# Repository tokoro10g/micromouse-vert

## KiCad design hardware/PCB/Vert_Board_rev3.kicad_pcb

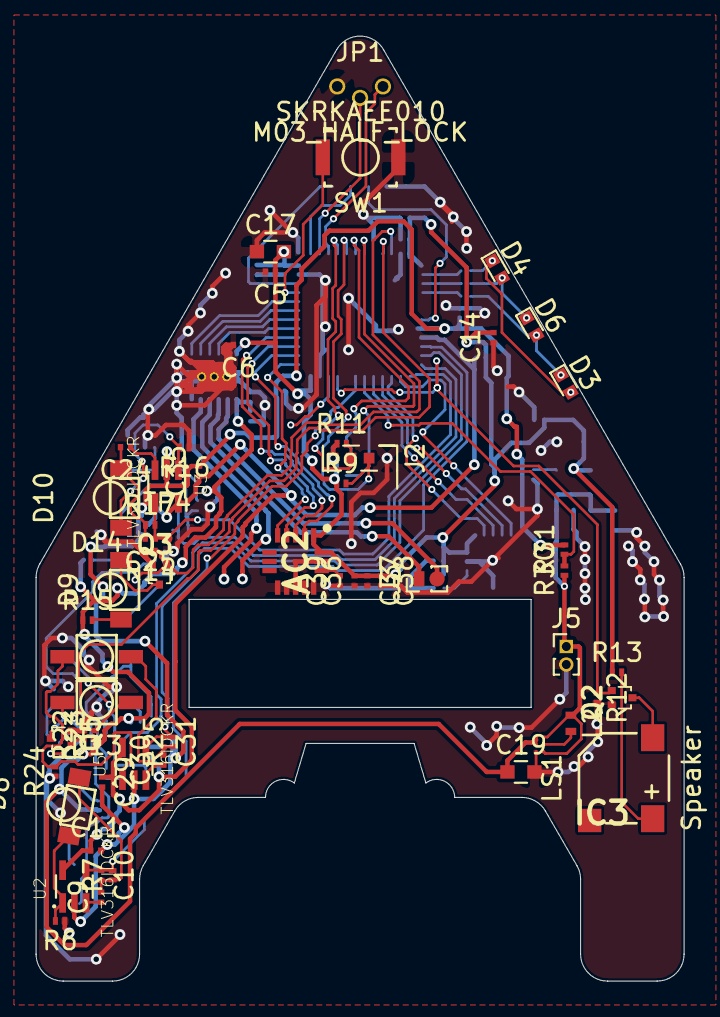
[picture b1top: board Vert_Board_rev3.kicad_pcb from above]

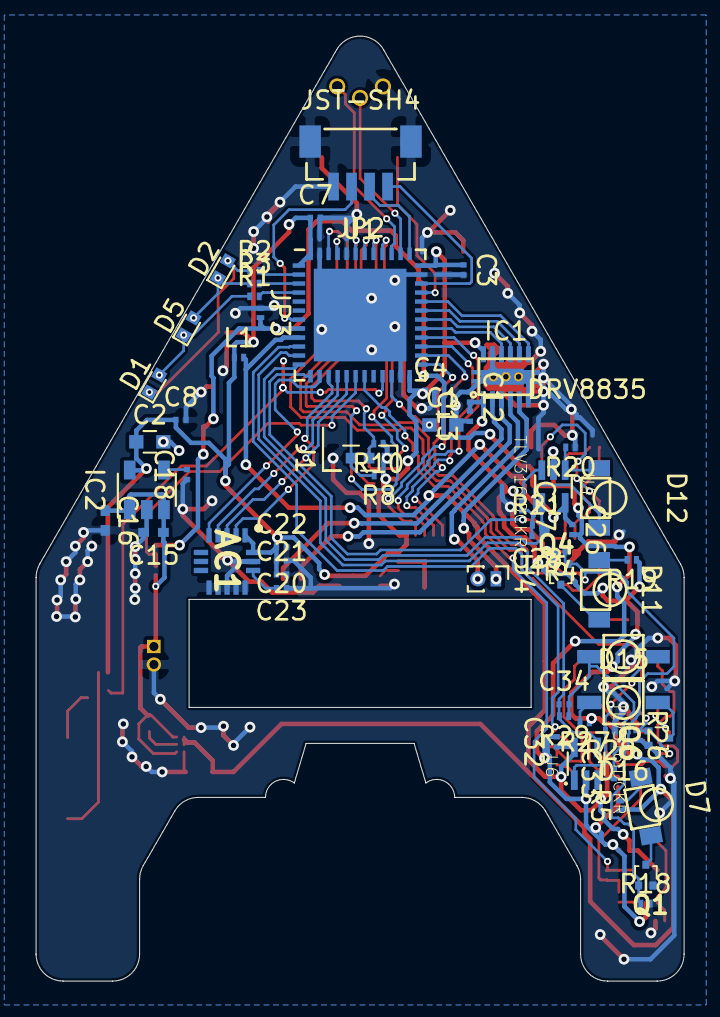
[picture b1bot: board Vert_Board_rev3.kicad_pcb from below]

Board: 4 copper layers, 36.0 x 52.5 mm, 117 parts (59 on the bottom side), 79 nets.

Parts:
AC1, AC2: ICM-20602; QFN50P300X300X75-16N
C1, C2, C19: 4.7u; C_0603
C3, C4, C5, C6, C7, C8, C11, C12, C14, C21, C23, C26, C29, C32, C35, C37, C39: 0.1u; C_0201_NoSilk
C9, C24, C27, C30, C33: 0.01u(NC); C_0201_NoSilk
C10, C25, C28, C31, C34: 22p; C_0201_NoSilk
C13: 22u; C_0201_NoSilk
C15: 2.2u; C_0402_NoSilk
C16: 1u; C_0402_NoSilk
C17: 10u; C_0603
C18, C20, C36: 0.01u; C_0201_NoSilk
C22, C38: 2.2u; C_0201_NoSilk
D1, D2, D3, D4, D5, D6: LED; LED_0402
D7, D9, D11: VSMB294008G; VSMB2943SL
D8, D10, D12: VEMD2020X01; VEMD2023SL
D13, D15: VSMB294008G
D14, D16: VEMD2020X01; VEMD2020
IC1: DRV8835
IC2: TAR5SB33; SOT-23-5
IC3: TPS6124x; BGA6C40P2X3_125X85X63
J1, J2: Conn_01x04; Pin_Header_Straight_1x04_Pitch1.00mm_SMD_Pin1Right
J3, J4, J5: Conn_01x02; Pin_Header_Straight_1x02_Pitch1.00mm
JP1: M03_HALF_LOCK
JP2: JST-SH4
JP3: Jumper_NC_Small; R_0201_NoSilk
L1: 10Z; R_0201_NoSilk
L2: 1u; R_0402_NoSilk
LS1: Speaker; SMT-0540-S-R
Q1, Q3, Q4, Q5, Q6: NTK3134NT1G; SOT-723
Q2: Q_NMOS_GSD; SOT-723
R1, R2, R3: 470; R_0201_NoSilk
R4, R8, R9, R10, R11, R12, R14, R18, R22, R26: 47k; R_0201_NoSilk
R5, R15, R19, R23, R27: 20; R_0201_NoSilk
R6, R16, R20, R24, R28, R30, R31: 500k; R_0201_NoSilk
R7, R17, R21, R25, R29: 1M; R_0201_NoSilk
R13: 22; R_0201_NoSilk
SW1: SKRKAEE010; ALPS-SKRK
TP4, TP6: TEST; Measurement_Point_Round-SMD-Pad_Small
U1: STM32F411CEUx; QFN-48-1EP_7x7mm_Pitch0.5mm
U2, U3, U4, U5, U6: TLV316IDCKR; SOT65P210X110-5N

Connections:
+5V: C12.2, C13.2, C19.1, IC1.1, IC3.B2, IC3.C2, R5.1, R15.1, R19.1, R23.1, R27.1
+BATT: C15.1, C16.1, IC2.1, IC2.3, IC3.A1, IC3.C1, J5.1, L2.1, R30.1
/Buzzer/BUZZER: Q2.1, R12.1, U1.21
/MCU/IMU1_MISO: AC1.4, U1.16
/MCU/IMU1_MOSI: AC1.3, U1.17
/MCU/IMU1_NSS: AC1.5, U1.14
/MCU/IMU1_SCK: AC1.2, U1.15
/MCU/IMU2_MISO: AC2.4, U1.27
/MCU/IMU2_MOSI: AC2.3, U1.28
/MCU/IMU2_NSS: AC2.5, U1.25
/MCU/IMU2_SCK: AC2.2, U1.26
/MCU/IRLED1: Q5.1, Q6.1, R22.1, R26.1, U1.45
/MCU/IRLED2: Q1.1, Q3.1, Q4.1, R4.1, R14.1, R18.1, U1.46
/MCU/MOTOR_LA: IC1.8, U1.31
/MCU/MOTOR_LB: IC1.7, U1.32
/MCU/MOTOR_RA: IC1.10, U1.29
/MCU/MOTOR_RB: IC1.9, U1.30
/MCU/NRST: JP2.2, U1.7
/MCU/SWCLK: JP2.3, U1.37
/MCU/SWDIO: JP2.4, U1.34
/MCU/UI_LED1: R2.2, U1.2
/MCU/UI_LED2: R3.2, U1.3
/MCU/UI_LED3: R1.2, U1.4
/MCU/UI_SWITCH: SW1.1, U1.33
/MCU/USART_MISO: JP1.1, U1.39
/MCU/USART_MOSI: JP1.2, U1.38
/Motor_L/ENCLA: J2.3, R11.2, U1.40
/Motor_L/ENCLB: J2.2, R9.2, U1.41
/Motor_L/ENCRA: J1.2, R8.2, U1.43
/Motor_L/ENCRB: J1.3, R10.2, U1.42
/OpticalSensor_FRONT/IR_SENS: C10.1, R7.2, U1.19, U2.4
/OpticalSensor_IRLB/IR_SENS: C25.1, R17.2, TP4.1, U1.13, U3.4
/OpticalSensor_IRLF/IR_SENS: C34.1, R29.2, U1.11, U6.4
/OpticalSensor_IRRB/IR_SENS: C28.1, R21.2, TP6.1, U1.12, U4.4
/OpticalSensor_IRRF/IR_SENS: C31.1, R25.2, U1.10, U5.4
GND: AC1.9, AC1.10, AC1.11, AC1.12, AC1.13, AC1.15, AC2.9, AC2.10, AC2.11, AC2.12, AC2.13, AC2.15, C1.2, C2.2, C3.2, C4.2, C5.2, C6.2, C7.2, C8.2, C12.1, C13.1, C14.1, C15.2, C16.2, C17.1, C18.1, C19.2, C20.1, C21.2, C22.2, C23.1, C36.1, C37.2, C38.2, C39.1, IC1.0, IC1.6, IC1.11, IC2.2, IC3.A2, J1.1, J2.1, J5.2, JP1.3, JP2.0, JP2.1, JP3.1, Q1.2, Q2.2, Q3.2, Q4.2, Q5.2, Q6.2, R4.2, R6.1, R12.2, R14.2, R16.1, R18.2, R20.1, R22.2, R24.1, R26.2, R28.1, SW1.2, U1.23, U1.35, U1.44, U1.47, U1.49
GNDA: C11.2, C26.2, C29.2, C32.2, C35.2, JP3.2, R31.2, U1.8, U2.2, U3.2, U4.2, U5.2, U6.2
unnamed: AC1.14, C23.2
unnamed: AC2.14, C39.2
unnamed: C1.1, U1.22
unnamed: C9.1, U2.3
unnamed: C9.2, C10.2, D8.2, R7.1
unnamed: C18.2, IC2.4
unnamed: C24.1, U3.3
unnamed: C24.2, C25.2, D10.2, R17.1
unnamed: C27.1, U4.3
unnamed: C27.2, C28.2, D12.2, R21.1
unnamed: C30.1, U5.3
unnamed: C30.2, C31.2, D14.2, R25.1
unnamed: C33.1, U6.3
unnamed: C33.2, C34.2, D16.2, R29.1
unnamed: D1.1, D2.2, D3.2, D4.1, R2.1
unnamed: D1.2, D3.1, D5.1, D6.2, R1.1
unnamed: D2.1, D4.2, D5.2, D6.1, R3.1
unnamed: D7.1, Q1.3
unnamed: D7.2, R5.2
unnamed: D8.1, R6.2, U2.1
unnamed: D9.1, Q3.3
unnamed: D9.2, R15.2
unnamed: D10.1, R16.2, U3.1
unnamed: D11.1, Q4.3
unnamed: D11.2, R19.2
unnamed: D12.1, R20.2, U4.1
unnamed: D13.1, Q5.3
unnamed: D13.2, R23.2
unnamed: D14.1, R24.2, U5.1
unnamed: D15.1, Q6.3
unnamed: D15.2, R27.2
unnamed: D16.1, R28.2, U6.1
unnamed: IC1.2, J3.2
unnamed: IC1.3, J3.1
unnamed: IC1.4, J4.2
unnamed: IC1.5, J4.1
unnamed: IC3.B1, L2.2
unnamed: LS1.1, R13.2
unnamed: LS1.2, Q2.3
unnamed: R30.2, R31.1, U1.18
VDD: AC1.1, AC1.16, AC2.1, AC2.16, C2.1, C3.1, C4.1, C5.1, C6.1, C7.1, C8.1, C14.2, C17.2, C20.2, C21.1, C22.1, C36.2, C37.1, C38.1, IC1.12, IC2.5, J1.4, J2.4, L1.1, R8.1, R9.1, R10.1, R11.1, R13.1, U1.1, U1.24, U1.36, U1.48
VDDA: C11.1, C26.1, C29.1, C32.1, C35.1, L1.2, U1.9, U2.5, U3.5, U4.5, U5.5, U6.5

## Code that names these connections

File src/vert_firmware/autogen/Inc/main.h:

/**
  ******************************************************************************
  * File Name          : main.h
  * Description        : This file contains the common defines of the application
  ******************************************************************************
  ** This notice applies to any and all portions of this file
  * that are not between comment pairs USER CODE BEGIN and
  * USER CODE END. Other portions of this file, whether 
  * inserted by the user or by software development tools
  * are owned by their respective copyright owners.
  *
  * COPYRIGHT(c) 2017 STMicroelectronics
  *
  * Redistribution and use in source and binary forms, with or without modification,
  * are permitted provided that the following conditions are met:
  *   1. Redistributions of source code must retain the above copyright notice,
  *      this list of conditions and the following disclaimer.
  *   2. Redistributions in binary form must reproduce the above copyright notice,
  *      this list of conditions and the following disclaimer in the documentation
  *      and/or other materials provided with the distribution.
  *   3. Neither the name of STMicroelectronics nor the names of its contributors
  *      may be used to endorse or promote products derived from this software
  *      without specific prior written permission.
  *
  * THIS SOFTWARE IS PROVIDED BY THE COPYRIGHT HOLDERS AND CONTRIBUTORS "AS IS"
  * AND ANY EXPRESS OR IMPLIED WARRANTIES, INCLUDING, BUT NOT LIMITED TO, THE
  * IMPLIED WARRANTIES OF MERCHANTABILITY AND FITNESS FOR A PARTICULAR PURPOSE ARE
  * DISCLAIMED. IN NO EVENT SHALL THE COPYRIGHT HOLDER OR CONTRIBUTORS BE LIABLE
  * FOR ANY DIRECT, INDIRECT, INCIDENTAL, SPECIAL, EXEMPLARY, OR CONSEQUENTIAL
  * DAMAGES (INCLUDING, BUT NOT LIMITED TO, PROCUREMENT OF SUBSTITUTE GOODS OR
  * SERVICES; LOSS OF USE, DATA, OR PROFITS; OR BUSINESS INTERRUPTION) HOWEVER
  * CAUSED AND ON ANY THEORY OF LIABILITY, WHETHER IN CONTRACT, STRICT LIABILITY,
  * OR TORT (INCLUDING NEGLIGENCE OR OTHERWISE) ARISING IN ANY WAY OUT OF THE USE
  * OF THIS SOFTWARE, EVEN IF ADVISED OF THE POSSIBILITY OF SUCH DAMAGE.
  *
  ******************************************************************************
  */
/* Define to prevent recursive inclusion -------------------------------------*/
#ifndef __MAIN_H
#define __MAIN_H
  /* Includes ------------------------------------------------------------------*/

/* USER CODE BEGIN Includes */

/* USER CODE END Includes */

/* Private define ------------------------------------------------------------*/

#define TIM2_CH3_Buzzer_Pin GPIO_PIN_10
#define TIM2_CH3_Buzzer_GPIO_Port GPIOB
#define MOTOR_RA_Pin GPIO_PIN_8
#define MOTOR_RA_GPIO_Port GPIOA
#define MOTOR_RB_Pin GPIO_PIN_9
#define MOTOR_RB_GPIO_Port GPIOA
#define MOTOR_LA_Pin GPIO_PIN_10
#define MOTOR_LA_GPIO_Port GPIOA
#define MOTOR_LB_Pin GPIO_PIN_11
#define MOTOR_LB_GPIO_Port GPIOA
#define GPIO_IN_Button_Pin GPIO_PIN_12
#define GPIO_IN_Button_GPIO_Port GPIOA
#define IRLED1_Pin GPIO_PIN_8
#define IRLED1_GPIO_Port GPIOB
#define IRLED2_Pin GPIO_PIN_9
#define IRLED2_GPIO_Port GPIOB

/* USER CODE BEGIN Private defines */

/* USER CODE END Private defines */

void _Error_Handler(char *, int);

#define Error_Handler() _Error_Handler(__FILE__, __LINE__)

/**
  * @}
  */ 

/**
  * @}
*/ 

#endif /* __MAIN_H */
/************************ (C) COPYRIGHT STMicroelectronics *****END OF FILE****/

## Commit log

2017-10-29 壁センサまわり実装中
2017-10-29 制御用コードのインポート，floatをprintできるように
2017-11-06 軌道キュー・UIを移植，軌道追従の基本機能の動作を確認
2017-11-06 addし忘れ…
2017-11-11 探索・最短走行を実装．壁トレース制御を調整中．
2017-11-14 クラシックサイズモード・クォーターサイズモードを実装．センサのキャリブレーション等も完了．
2017-11-15 軽微な不具合の修正
2017-11-16 探索・メニューまわりのバグ修正 fixes #1.
2017-11-16 最適化でIRLEDの動作が消えることがあるのを修正
2017-11-16 迷路端で既知区間加速が起こらないバグを修正．1マスの場合に加速しないように変更．
2017-11-16 センシング前の距離パラメータを追加 [experimental]
2017-11-16 迷路ダンプモードを追加．その他雑多な変更．
2017-11-16 壁パラメータ暫定
2018-08-19 ブザーの音量変更機能を追加
2018-08-19 迷路情報をFLASHに読み書きする機能を追加
2018-08-19 メロディとデバッグ用のブザー音を追加
2018-08-19 サーキットモードを追加(注:迷路サイズベタ書き)
2018-08-19 サーキットモードのデバッグ用のシーケンスを追加
2018-08-19 ターン前の距離を調整
2018-08-19 機体パラメータの調整
2018-08-19 走行パラメータの調整
2018-08-19 機体の制御に使用するパラメータの調整
2018-08-19 壁センサまわりの補正コードを変更
2018-08-19 バグった挙動をひとまず治すためだけのコード(後で解決する)
2018-08-19 雑多なもの
2018-08-19 ビルドの潜在的な不具合を解消
2018-08-19 clangのlanguage serverに読ませるためのファイルを作成
2018-08-19 libmazesolverの更新
